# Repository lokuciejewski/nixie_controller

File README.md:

# Controller/clock for mini Nixie I2C modules

STM32-based controller board that uses 4 [nixie modules](https://github.com/lokuciejewski/nixie_module) to display the current time. The modules can be changed at any time the board is off and swapped if the nixie tube goes bad or the user wants to insert a different nixie tube.

The board uses a STM32U031 microcontroller coupled with DS3231 RTC to achieve low power, reliable timekeeping.
For High Voltage for the nixie tubes, it uses a premade nixie PSU 160-180V (available on aliexpress). It uses a single cell CR2032 battery to keep the time when the module is not connected. For communication, it uses a serial interface over the USB-C port (which also serves as the power input). The board features 3 programmable buttons and two LEDs for signalling the system status.

Note: V1 version of the board contains multiple test points and additional inputs which will be removed in the V2 version.

## Building

Prerequisites:

- Rust
- `cargo`

To build, simply run `cargo build --release`

## Flashing

The board is flashed using `probe-rs`, which can utilize a range of multiple programmers, for example an ST-Link.
Connect the programmer to the J3 and run `cargo run --release`.

## Operation

Currently, the time can only be set using the serial port and the `comm.py` script.

The serial protocol for talking to the board can be found [in the `serial` directory](./src/serial/)

## Planned features

V2 will have an option to wire 1 or 2 neon tubes between the hour and minute displays (since not all nixie tubes come with a comma).

It may also be equipped with the human presence sensor to only light up when it can detect a human.

A console interface is planned to utilize all features of the board (such as programming inputs, time, etc.)

The board has a second serial available on pins which may be used for wireless time access via e.g. an esp32.

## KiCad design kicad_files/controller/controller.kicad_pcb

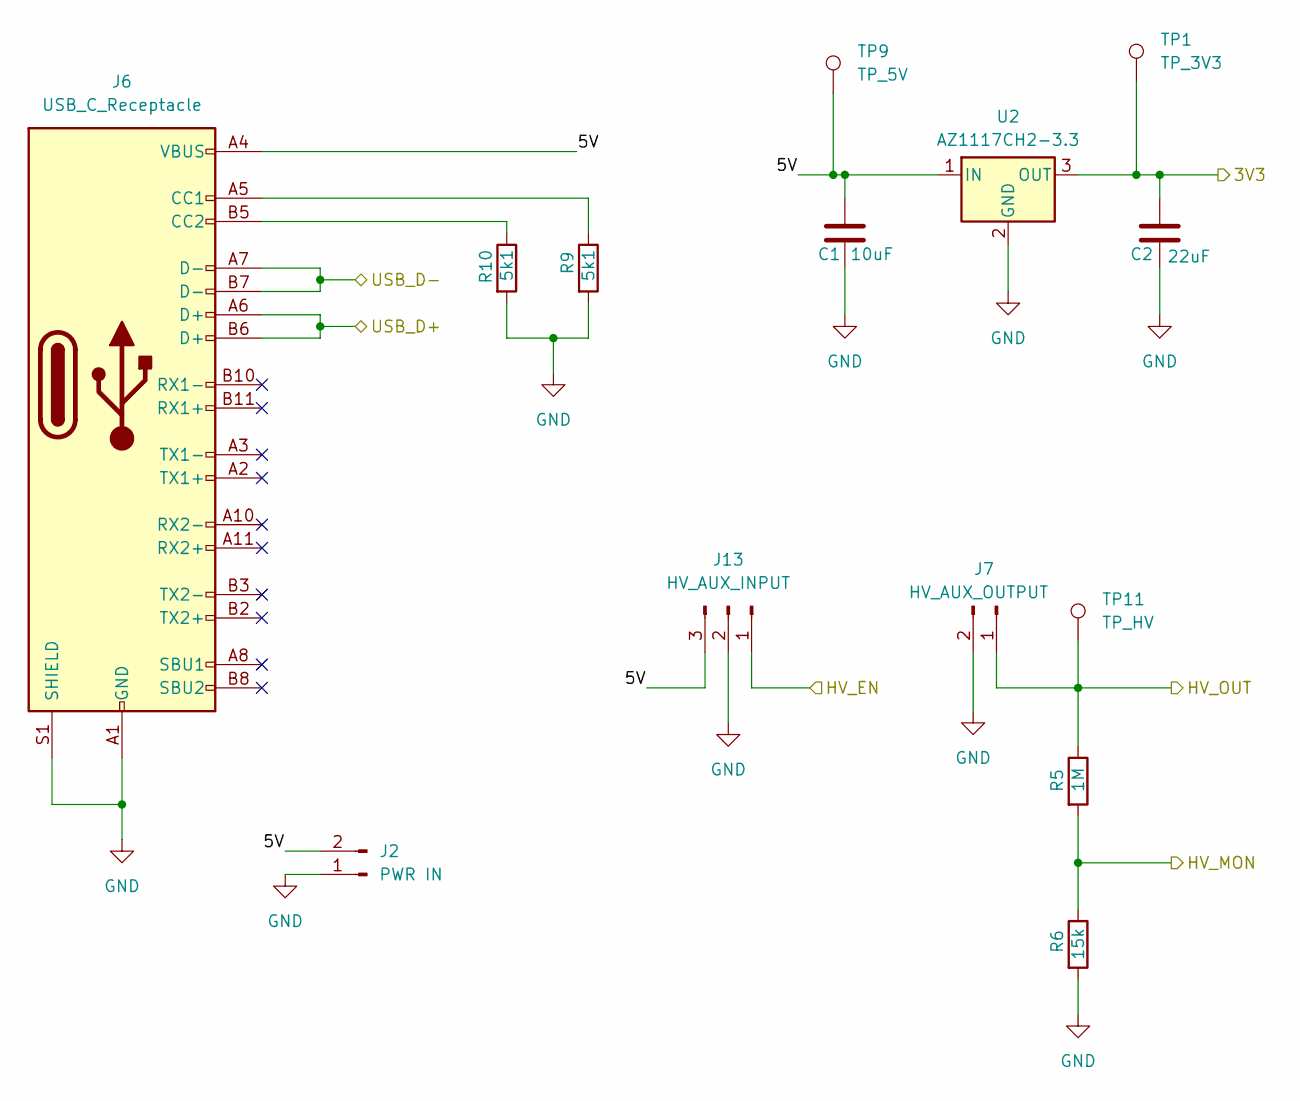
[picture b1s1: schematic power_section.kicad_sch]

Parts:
C1: 10uF; C_0603_1608Metric_Pad1.08x0.95mm_HandSolder
C2: 22uF; C_0603_1608Metric_Pad1.08x0.95mm_HandSolder
J2: PWR IN; PinHeader_1x02_P2.54mm_Vertical
J6: USB_C_Receptacle; USB_C_Receptacle_GCT_USB4085
J7: HV_AUX_OUTPUT; PinHeader_1x02_P2.54mm_Vertical
J13: HV_AUX_INPUT; PinHeader_1x03_P2.54mm_Vertical
R5: 1M; R_0805_2012Metric_Pad1.20x1.40mm_HandSolder
R6: 15k; R_0603_1608Metric_Pad0.98x0.95mm_HandSolder
R9, R10: 5k1; R_0603_1608Metric_Pad0.98x0.95mm_HandSolder
TP1: TP_3V3; TestPoint_Pad_D1.0mm
TP9: TP_5V; TestPoint_Pad_D1.0mm
TP11: TP_HV; TestPoint_Pad_D1.0mm
U2: AZ1117CH2-3.3; SOT-223-3_TabPin2

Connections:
/MCU/3V3: C2.1, TP1.1, U2.3 (OUT); also elsewhere on the board
/MCU/HV_EN: J13.1; also elsewhere on the board
/MCU/HV_MON: R5.2, R6.1; also elsewhere on the board
/MCU/USB_D+: J6.A6 (D+), J6.B6 (D+); also elsewhere on the board
/MCU/USB_D-: J6.A7 (D-), J6.B7 (D-); also elsewhere on the board
/Nixie Module Mounts/HV0: J7.1, R5.1, TP11.1; also elsewhere on the board
/Power Section/5V: C1.1, J2.2, J6.A4 (VBUS), J6.A9 (VBUS), J6.B4 (VBUS), J6.B9 (VBUS), J13.3, TP9.1, U2.1 (IN)
GND: C1.2, C2.2, J2.1, J6.A1 (GND), J6.A12 (GND), J6.B1 (GND), J6.B12 (GND), J6.S1 (SHIELD), J7.2, J13.2, R6.2, R9.2, R10.2, U2.2 (GND); also elsewhere on the board
unnamed: J6.A5 (CC1), R9.1
unnamed: J6.B5 (CC2), R10.1

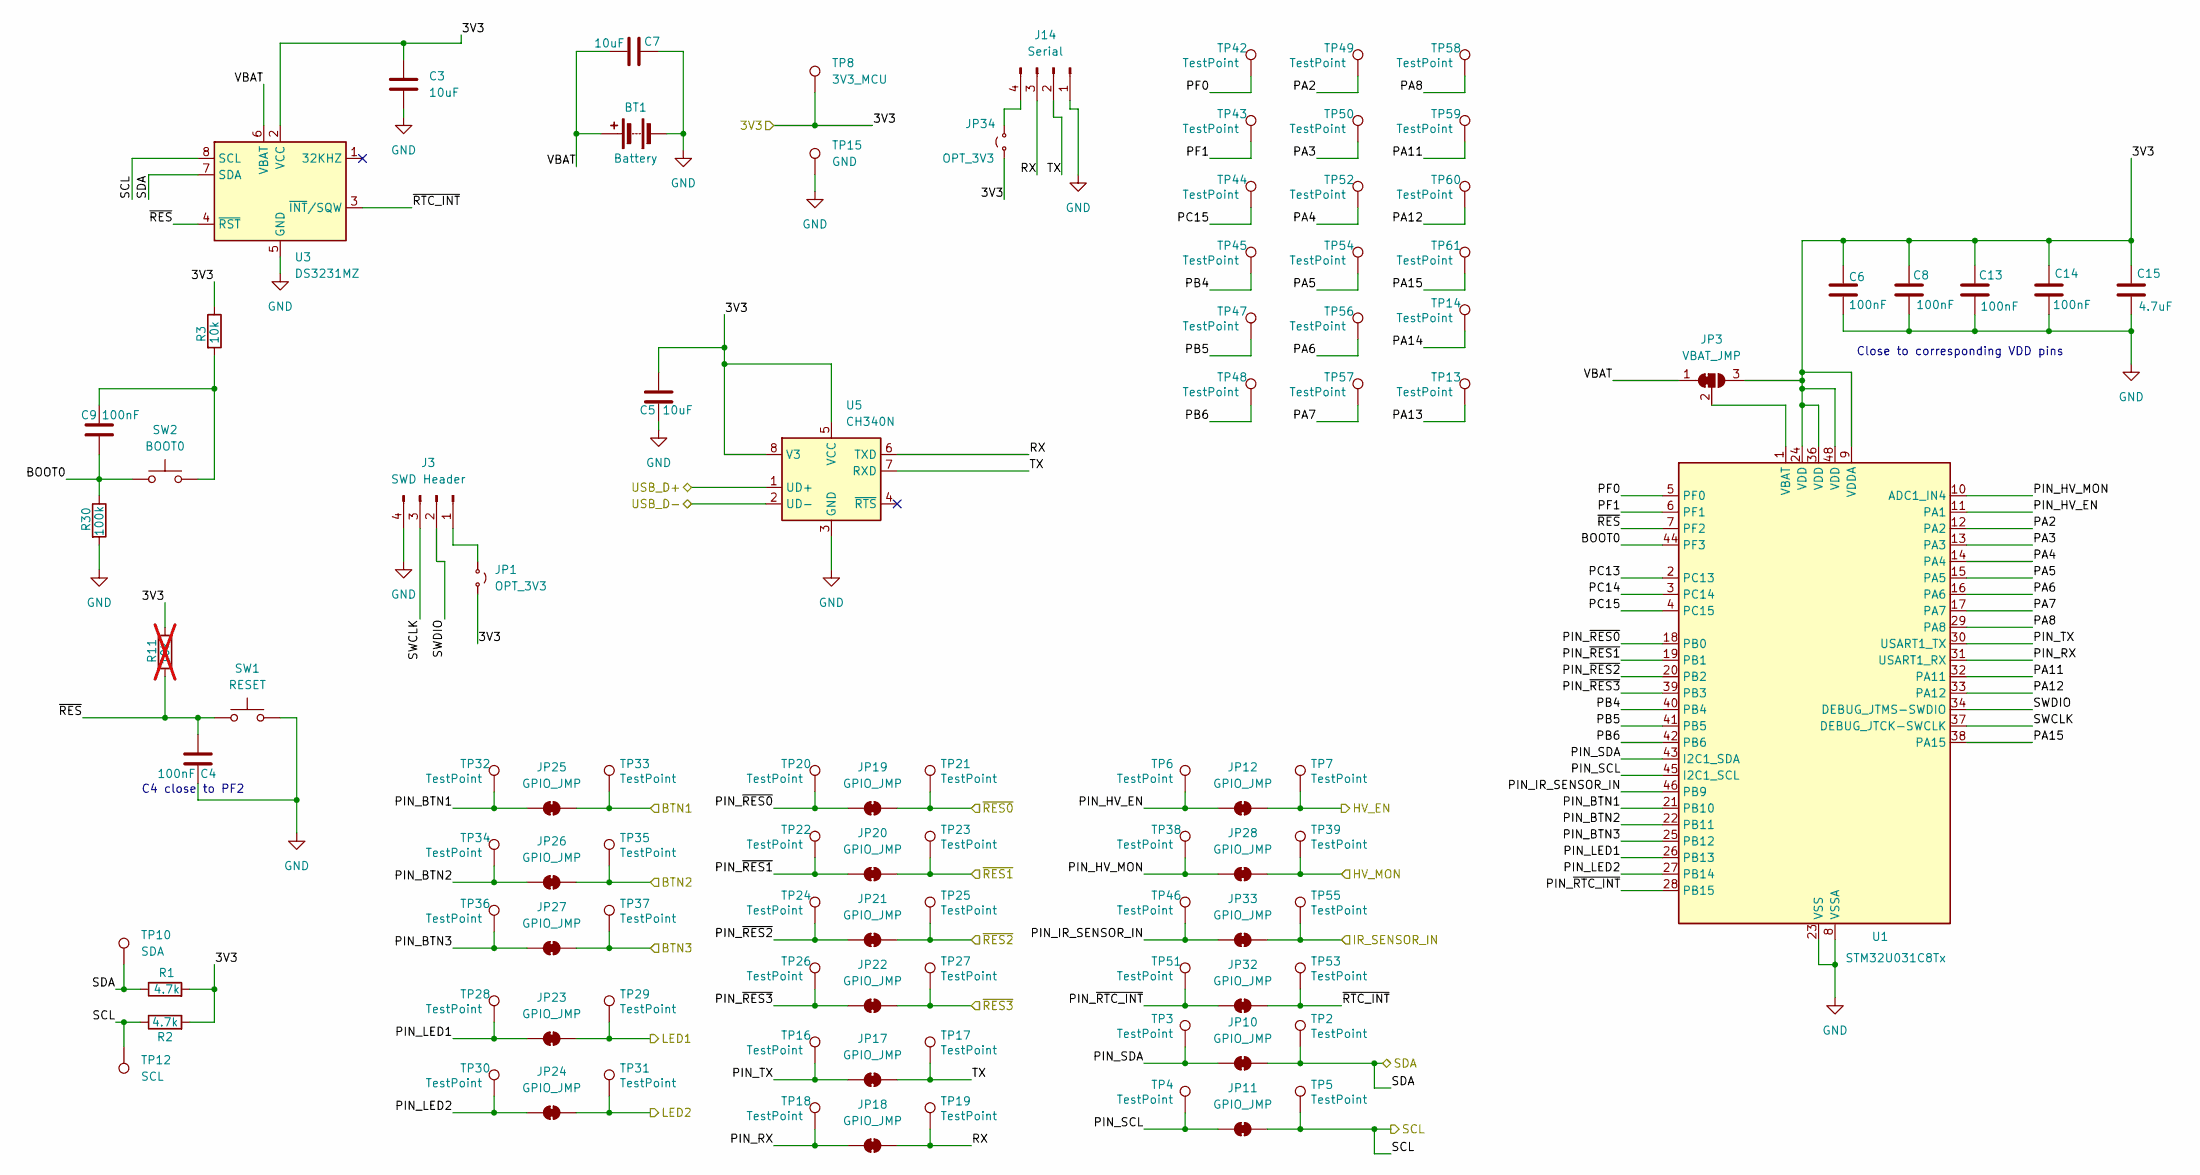
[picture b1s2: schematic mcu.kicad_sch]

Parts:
BT1: Battery; BatteryHolder_Keystone_1060_1x2032
C3, C5, C7: 10uF; C_0603_1608Metric_Pad1.08x0.95mm_HandSolder
C4, C6, C8, C9, C13, C14: 100nF; C_0603_1608Metric_Pad1.08x0.95mm_HandSolder
C15: 4.7uF; C_0603_1608Metric_Pad1.08x0.95mm_HandSolder
J3: SWD Header; PinHeader_1x04_P2.54mm_Vertical
J14: Serial; PinHeader_1x04_P2.54mm_Vertical
JP1, JP34: OPT_3V3; SolderJumper-2_P1.3mm_Open_RoundedPad1.0x1.5mm
JP3: VBAT_JMP; SolderJumper-3_P1.3mm_Bridged2Bar12_RoundedPad1.0x1.5mm_Num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
JP10, JP11, JP12, JP17, JP18, JP19, JP20, JP21, JP22, JP23, JP24, JP25, JP26, JP27, JP28, JP32, JP33: GPIO_JMP; SolderJumper-2_P1.3mm_Bridged2Bar_RoundedPad1.0x1.5mm
R1, R2: 4.7k; R_0603_1608Metric_Pad0.98x0.95mm_HandSolder
R3: 10k; R_0603_1608Metric_Pad0.98x0.95mm_HandSolder
R11: 10k; R_0603_1608Metric_Pad0.98x0.95mm_HandSolder; not fitted
R30: 100k; R_0603_1608Metric_Pad0.98x0.95mm_HandSolder
SW1: RESET; SW_SPST_TL3305A
SW2: BOOT0; SW_SPST_TL3305A
TP2, TP3, TP4, TP5, TP6, TP7, TP13, TP14, TP16, TP17, TP18, TP19, TP20, TP21, TP22, TP23, TP24, TP25, TP26, TP27, TP28, TP29, TP30, TP31, TP32, TP33, TP34, TP35, TP36, TP37, TP38, TP39, TP42, TP43, TP44, TP45, TP46, TP47, TP48, TP49, TP50, TP51, TP52, TP53, TP54, TP55, TP56, TP57, TP58, TP59, TP60, TP61: TestPoint; TestPoint_Pad_D1.0mm
TP8: 3V3_MCU; TestPoint_Pad_D1.0mm
TP10: SDA; TestPoint_Pad_D1.0mm
TP12: SCL; TestPoint_Pad_D1.0mm
TP15: GND; TestPoint_Pad_D1.0mm
U1: STM32U031C8Tx; LQFP-48_7x7mm_P0.5mm
U3: DS3231MZ; SOIC-8_3.9x4.9mm_P1.27mm
U5: CH340N; JEITA_SOIC-8_3.9x4.9mm_P1.27mm

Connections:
/IO Section/BTN_1: JP25.2 (B), TP33.1; also elsewhere on the board
/IO Section/BTN_2: JP26.2 (B), TP35.1; also elsewhere on the board
/IO Section/BTN_3: JP27.2 (B), TP37.1; also elsewhere on the board
/IO Section/IR_SENSOR_OUT: JP33.2 (B), TP55.1; also elsewhere on the board
/IO Section/LED_1: JP23.2 (B), TP29.1; also elsewhere on the board
/IO Section/LED_2: JP24.2 (B), TP31.1; also elsewhere on the board
/MCU/3V3: C3.1, C5.1, C6.1, C8.1, C13.1, C14.1, C15.1, JP1.2 (B), JP3.3 (B), JP34.1 (A), R1.2, R2.2, R3.1, R11.1, TP8.1, U1.9 (VDDA), U1.24 (VDD), U1.36 (VDD), U1.48 (VDD), U3.2 (VCC), U5.5 (VCC), U5.8 (V3); also elsewhere on the board
/MCU/BOOT0: C9.1, R30.1, SW2.1, U1.44 (PF3)
/MCU/HV_EN: JP12.2 (B), TP7.1; also elsewhere on the board
/MCU/HV_MON: JP28.2 (B), TP39.1; also elsewhere on the board
/MCU/PA2: TP49.1, U1.12 (PA2)
/MCU/PA3: TP50.1, U1.13 (PA3)
/MCU/PA4: TP52.1, U1.14 (PA4)
/MCU/PA5: TP54.1, U1.15 (PA5)
/MCU/PA6: TP56.1, U1.16 (PA6)
/MCU/PA7: TP57.1, U1.17 (PA7)
/MCU/PA8: TP58.1, U1.29 (PA8)
/MCU/PA11: TP59.1, U1.32 (PA11)
/MCU/PA12: TP60.1, U1.33 (PA12)
/MCU/PA13: TP13.1
/MCU/PA14: TP14.1
/MCU/PA15: TP61.1, U1.38 (PA15)
/MCU/PB4: TP45.1, U1.40 (PB4)
/MCU/PB5: TP47.1, U1.41 (PB5)
/MCU/PB6: TP48.1, U1.42 (PB6)
/MCU/PC13: U1.2 (PC13)
/MCU/PC14: U1.3 (PC14)
/MCU/PC15: TP44.1, U1.4 (PC15)
/MCU/PF0: TP42.1, U1.5 (PF0)
/MCU/PF1: TP43.1, U1.6 (PF1)
/MCU/PIN_BTN1: JP25.1 (A), TP32.1, U1.21 (PB10)
/MCU/PIN_BTN2: JP26.1 (A), TP34.1, U1.22 (PB11)
/MCU/PIN_BTN3: JP27.1 (A), TP36.1, U1.25 (PB12)
/MCU/PIN_HV_EN: JP12.1 (A), TP6.1, U1.11 (PA1)
/MCU/PIN_HV_MON: JP28.1 (A), TP38.1, U1.10 (ADC1_IN4)
/MCU/PIN_IR_SENSOR_IN: JP33.1 (A), TP46.1, U1.46 (PB9)
/MCU/PIN_LED1: JP23.1 (A), TP28.1, U1.26 (PB13)
/MCU/PIN_LED2: JP24.1 (A), TP30.1, U1.27 (PB14)
/MCU/PIN_RX: JP18.1 (A), TP18.1, U1.31 (USART1_RX)
/MCU/PIN_SCL: JP11.1 (A), TP4.1, U1.45 (I2C1_SCL)
/MCU/PIN_SDA: JP10.1 (A), TP3.1, U1.43 (I2C1_SDA)
/MCU/PIN_TX: JP17.1 (A), TP16.1, U1.30 (USART1_TX)
/MCU/PIN_~RES0: JP19.1 (A), TP20.1, U1.18 (PB0)
/MCU/PIN_~RES1: JP20.1 (A), TP22.1, U1.19 (PB1)
/MCU/PIN_~RES2: JP21.1 (A), TP24.1, U1.20 (PB2)
/MCU/PIN_~RES3: JP22.1 (A), TP26.1, U1.39 (PB3)
/MCU/PIN_~RTC_INT: JP32.1 (A), TP51.1, U1.28 (PB15)
/MCU/RX: J14.3, JP18.2 (B), TP19.1, U5.6 (TXD)
/MCU/SCL: JP11.2 (B), R2.1, TP5.1, TP12.1, U3.8 (SCL); also elsewhere on the board
/MCU/SDA: JP10.2 (B), R1.1, TP2.1, TP10.1, U3.7 (SDA); also elsewhere on the board
/MCU/SWCLK: J3.3, U1.37 (DEBUG_JTCK-SWCLK)
/MCU/SWDIO: J3.2, U1.34 (DEBUG_JTMS-SWDIO)
/MCU/TX: J14.2, JP17.2 (B), TP17.1, U5.7 (RXD)
/MCU/USB_D+: U5.1 (UD+); also elsewhere on the board
/MCU/USB_D-: U5.2 (UD-); also elsewhere on the board
/MCU/VBAT: BT1.1 (+), C7.2, JP3.1 (A), U3.6 (VBAT)
/MCU/~RES0: JP19.2 (B), TP21.1; also elsewhere on the board
/MCU/~RES1: JP20.2 (B), TP23.1; also elsewhere on the board
/MCU/~RES2: JP21.2 (B), TP25.1; also elsewhere on the board
/MCU/~RES3: JP22.2 (B), TP27.1; also elsewhere on the board
/MCU/~RES: C4.1, R11.2, SW1.1, U1.7 (PF2), U3.4 (~RST)
/MCU/~RTC_INT: JP32.2 (B), TP53.1, U3.3 (~INT/SQW)
GND: BT1.2 (-), C3.2, C4.2, C5.2, C6.2, C7.1, C8.2, C13.2, C14.2, C15.2, J3.4, J14.1, R30.2, SW1.2, TP15.1, U1.8 (VSSA), U1.23 (VSS), U3.5 (GND), U5.3 (GND); also elsewhere on the board
unnamed: C9.2, R3.2, SW2.2
unnamed: J3.1, JP1.1 (A)
unnamed: J14.4, JP34.2 (B)
unnamed: JP3.2 (C), U1.1 (VBAT)
unnamed: U1.35 (VSS), U1.47 (VSS)

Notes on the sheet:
Close to corresponding VDD pins
C4 close to PF2

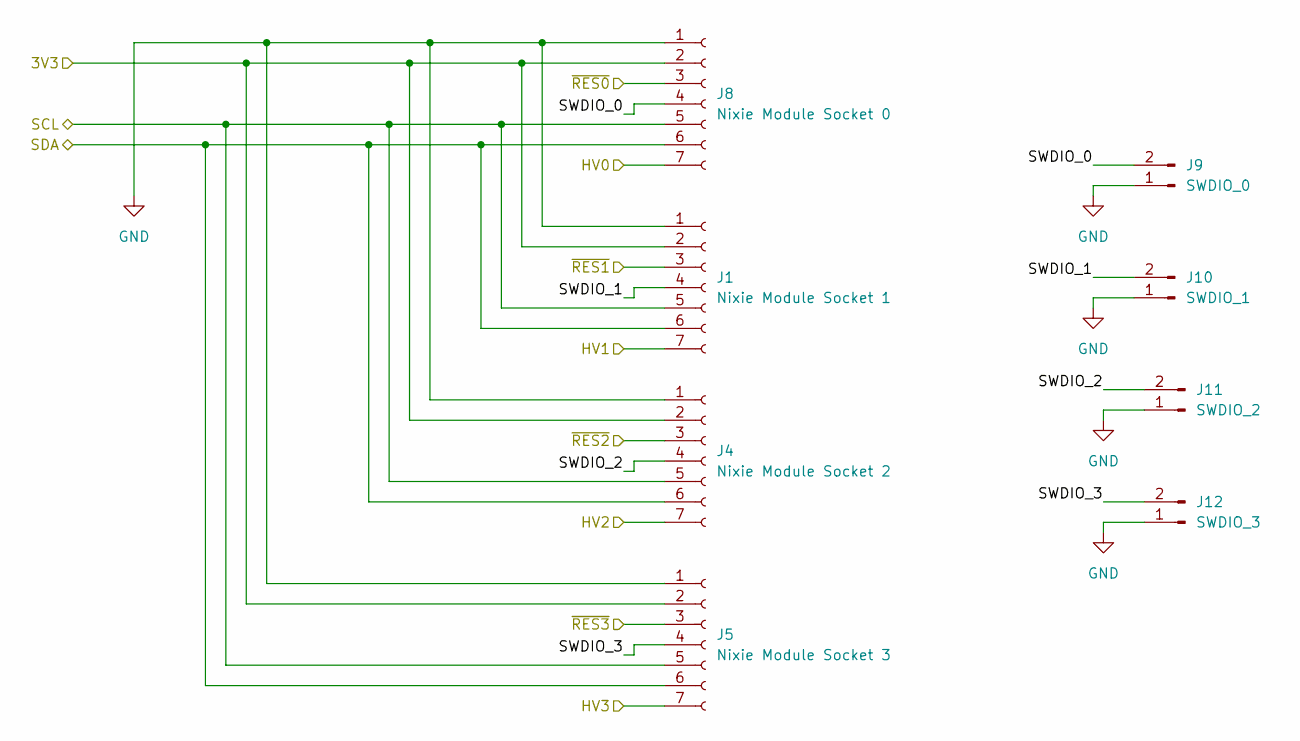
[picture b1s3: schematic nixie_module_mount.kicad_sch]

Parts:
J1: Nixie Module Socket 1; PinHeader_1x07_P2.54mm_Vertical
J4: Nixie Module Socket 2; PinHeader_1x07_P2.54mm_Vertical
J5: Nixie Module Socket 3; PinHeader_1x07_P2.54mm_Vertical
J8: Nixie Module Socket 0; PinHeader_1x07_P2.54mm_Vertical
J9: SWDIO_0; PinHeader_1x02_P2.54mm_Vertical
J10: SWDIO_1; PinHeader_1x02_P2.54mm_Vertical
J11: SWDIO_2; PinHeader_1x02_P2.54mm_Vertical
J12: SWDIO_3; PinHeader_1x02_P2.54mm_Vertical

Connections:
/MCU/3V3: J1.2, J4.2, J5.2, J8.2; also elsewhere on the board
/MCU/SCL: J1.5, J4.5, J5.5, J8.5; also elsewhere on the board
/MCU/SDA: J1.6, J4.6, J5.6, J8.6; also elsewhere on the board
/MCU/~RES0: J8.3; also elsewhere on the board
/MCU/~RES1: J1.3; also elsewhere on the board
/MCU/~RES2: J4.3; also elsewhere on the board
/MCU/~RES3: J5.3; also elsewhere on the board
/Nixie Module Mounts/HV0: J1.7, J4.7, J5.7, J8.7; also elsewhere on the board
/Nixie Module Mounts/SWDIO_0: J8.4, J9.2
/Nixie Module Mounts/SWDIO_1: J1.4, J10.2
/Nixie Module Mounts/SWDIO_2: J4.4, J11.2
/Nixie Module Mounts/SWDIO_3: J5.4, J12.2
GND: J1.1, J4.1, J5.1, J8.1, J9.1, J10.1, J11.1, J12.1; also elsewhere on the board

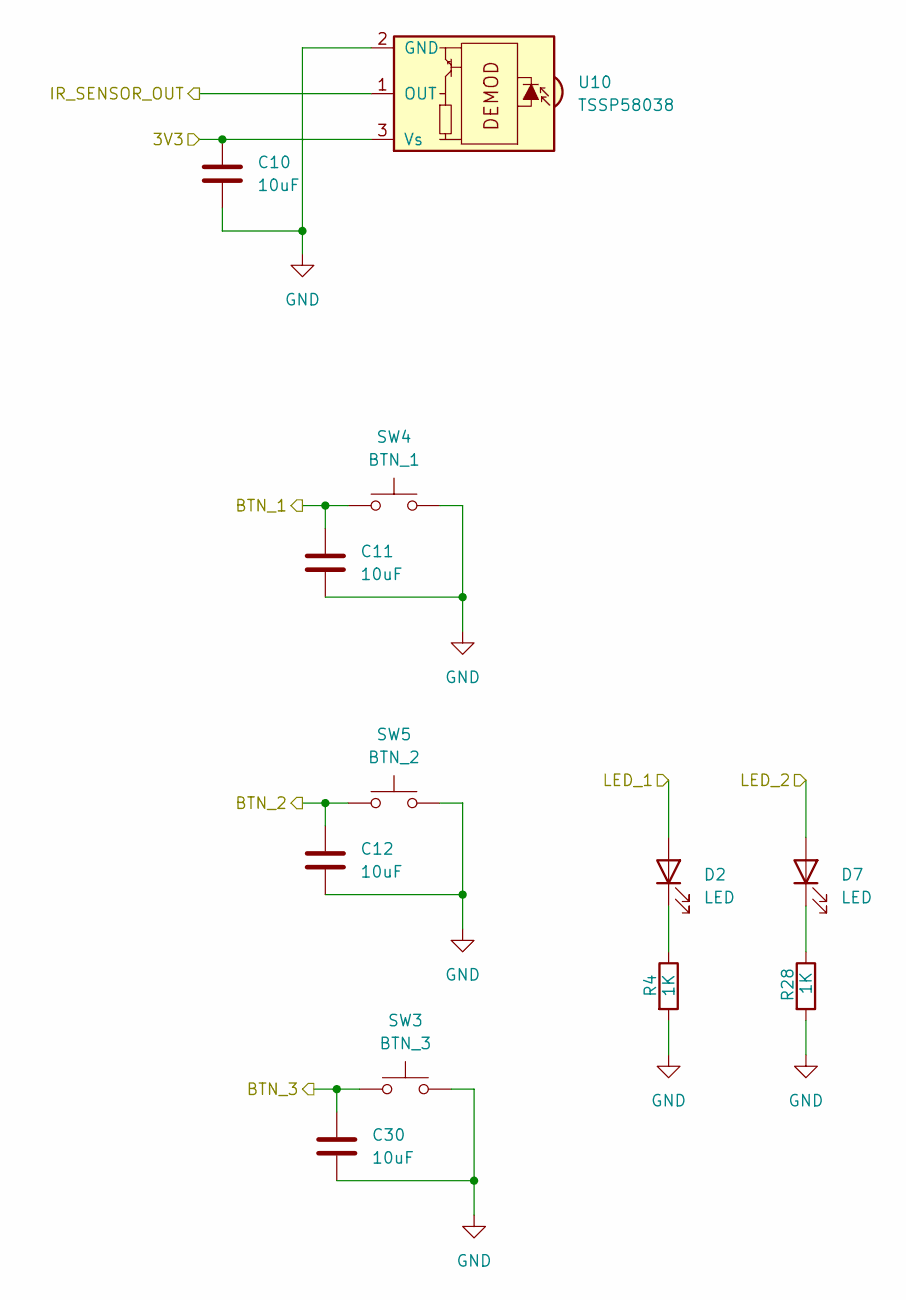
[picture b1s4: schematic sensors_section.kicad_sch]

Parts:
C10, C11, C12, C30: 10uF; C_0603_1608Metric_Pad1.08x0.95mm_HandSolder
D2, D7: LED; LED_0603_1608Metric_Pad1.05x0.95mm_HandSolder
R4, R28: 1K; R_0603_1608Metric_Pad0.98x0.95mm_HandSolder
SW3: BTN_3; SW_Tactile_SPST_Angled_PTS645Vx39-2LFS
SW4: BTN_1; SW_Tactile_SPST_Angled_PTS645Vx39-2LFS
SW5: BTN_2; SW_Tactile_SPST_Angled_PTS645Vx39-2LFS
U10: TSSP58038; Vishay_MINICAST-3Pin

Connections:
/IO Section/BTN_1: C11.1, SW4.1; also elsewhere on the board
/IO Section/BTN_2: C12.1, SW5.1; also elsewhere on the board
/IO Section/BTN_3: C30.1, SW3.1; also elsewhere on the board
/IO Section/IR_SENSOR_OUT: U10.1 (OUT); also elsewhere on the board
/IO Section/LED_1: D2.2 (A); also elsewhere on the board
/IO Section/LED_2: D7.2 (A); also elsewhere on the board
/MCU/3V3: C10.1, U10.3 (Vs); also elsewhere on the board
GND: C10.2, C11.2, C12.2, C30.2, R4.2, R28.2, SW3.2, SW4.2, SW5.2, U10.2 (GND); also elsewhere on the board
unnamed: D2.1 (K), R4.1
unnamed: D7.1 (K), R28.1

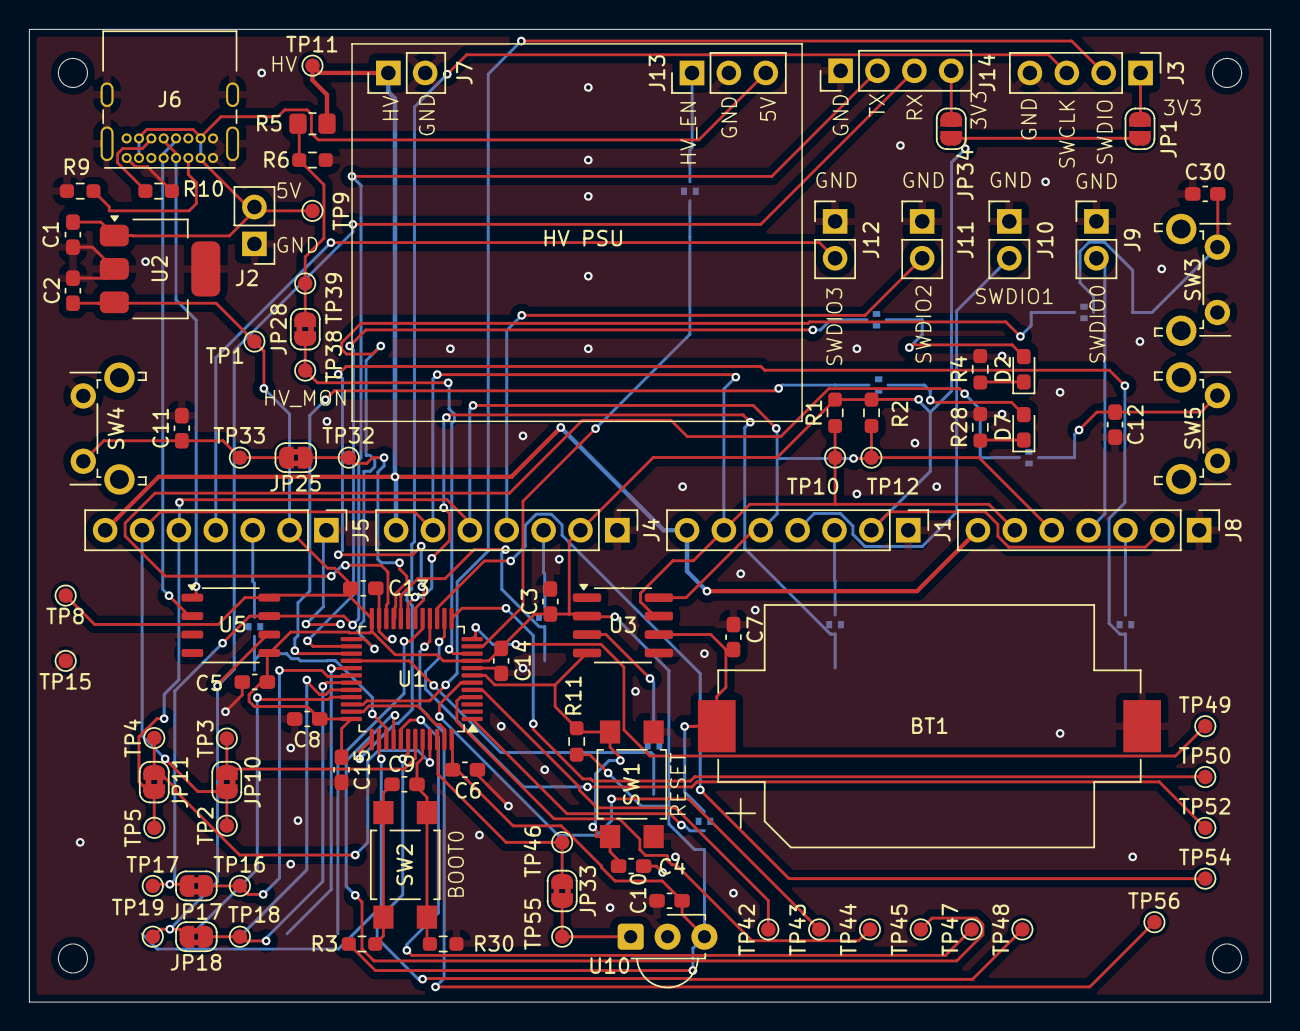
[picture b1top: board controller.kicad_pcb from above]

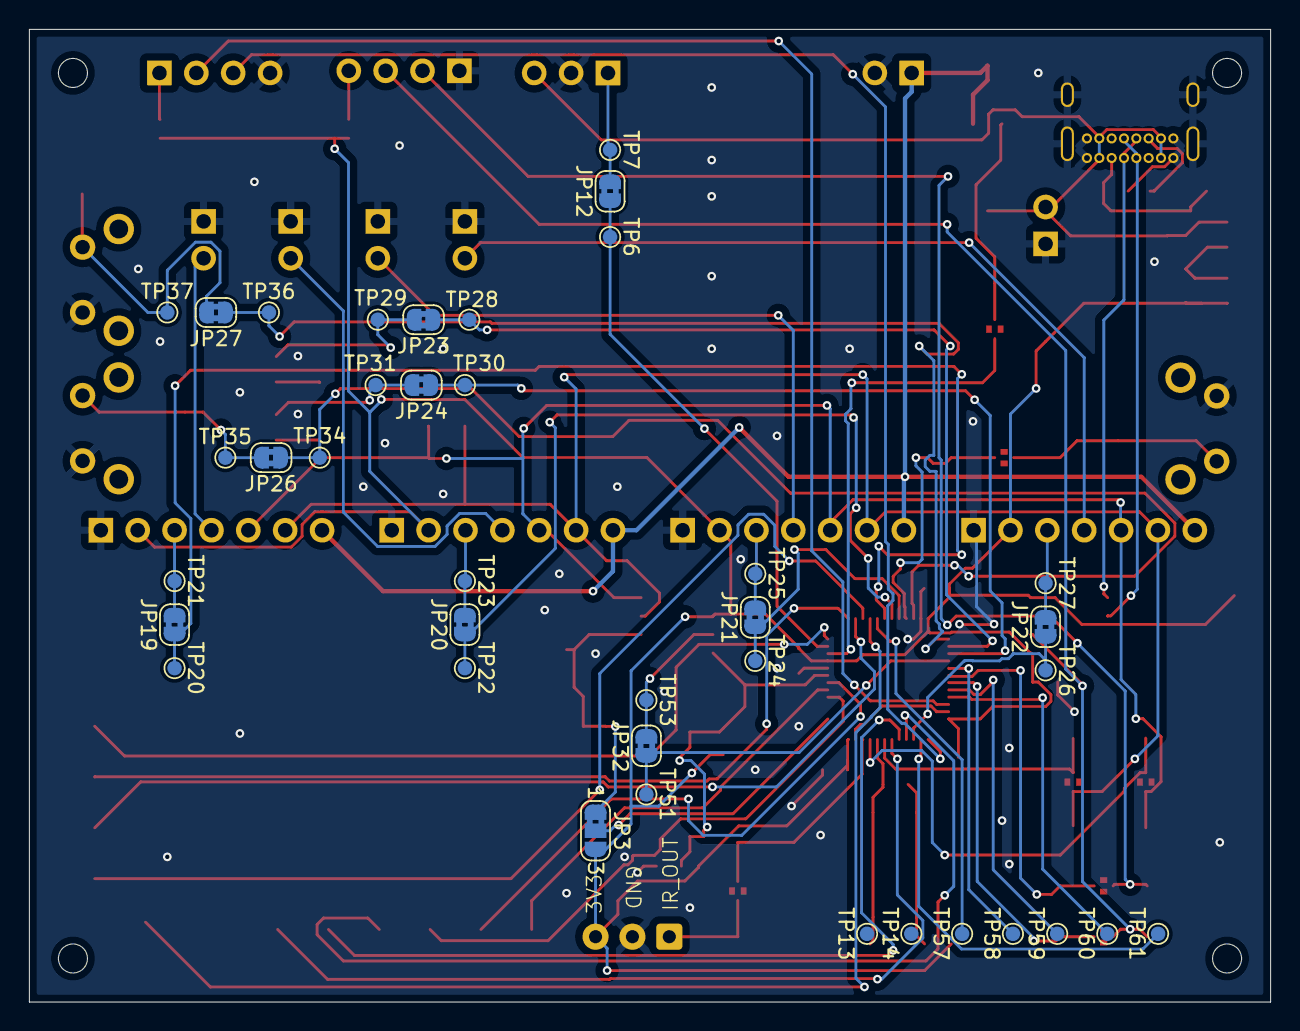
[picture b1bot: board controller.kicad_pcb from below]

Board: 2 copper layers, 85.5 x 67.0 mm, 133 parts (38 on the bottom side), 74 nets.

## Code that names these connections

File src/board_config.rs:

use embassy_stm32::peripherals::*;
use embedded_resources::resource_group;

#[resource_group]
pub(crate) struct ButtonResources {
    button_1: PB10,
    button_2: PB11,
    button_3: PB12,
}

#[resource_group]
pub(crate) struct LedResources {
    red: PB13,
    green: PB14,
}

#[resource_group]
pub(crate) struct IRSensorResources {
    detection: PB9
}

#[resource_group]
pub(crate) struct ModuleResources {
    reset_0: PB0,
    reset_1: PB1,
    reset_2: PB2,
    reset_3: PB3,
}

#[resource_group]
pub(crate) struct I2CResources {
    i2c_instance: I2C1,
    sda: PB7,
    scl: PB8,
}

#[resource_group]
pub(crate) struct UARTResources {
    uart_instance: USART1,
    tx: PA9,
    rx: PA10,
    tx_dma: DMA1_CH3,
    rx_dma: DMA1_CH4,
}

#[resource_group]
pub(crate) struct HVResources {
    hv_en: PA1,
    hv_mon: PA0,
}

#[resource_group]
pub(crate) struct RTCResources {
    sqw_int: PB15,
    int_channel: EXTI15
}

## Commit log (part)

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2025-04-06 added .gitignore, readme, .cargo
2025-04-09 added IR motion sensor
2025-06-26 changed target to STM32U031F8Px
2025-08-14 added board_config for evalboard/sample_1
2025-08-15 lowered i2c timeout to speed up the device discovery
2025-08-20 more sample 1 changes
2025-08-25 restructured repo, minor fixes
2025-08-28 separated tasks for most things, added rtc, simple clock mode
2025-08-28 fixed red led staying on in Normal state
2025-09-02 added setting + getting datetime via serial, added serial protocol
2025-10-14 updated dependencies, updated serial protocol
2025-10-14 fixed bugs in python script, fixed some serialization bugs, added separate commands module
2025-10-14 added initial state switching architecture
2026-01-06 updated refreshing policy
2026-01-06 added brightness setting
